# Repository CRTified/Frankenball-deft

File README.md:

# Frankenball-deft

This project is a replacement PCB for the Elecom Deft (non-pro) trackball.
Besides the basic functionality, it exposes two additional GPIO pins 
(also usable for debugging) and is powered by QMK (TODO) on an STM32F411.

The sensor used in the Elecom deft is an PWM3320.

Some additional soldering is required. 
The PCB is intended for SMT assembly by JLCPCB. 
The only extended part is the STM32F411, every other part is a basic component.

## Additional componens used

 - 0.5mm 6pin Clamshell FFC connector (PWM3320 Sensor)
   - https://aliexpress.com/item/1005003981823532.html
 - 0.5mm 12pin Clamshell FFC connector (Side button daughterboard)
   - https://aliexpress.com/item/1005003981823532.html
 - 4 pin JST ZH header (1.5mm pitch) (M1/M2/M3 daughterboard)
   - https://aliexpress.com/item/32763788431.html
 - 51146 Socket (USB connection)
   - https://aliexpress.com/item/4000818221650.html
 - Microswitch (Right mouse button)
   - https://aliexpress.com/item/4000682779339.html
   - https://aliexpress.com/item/4000555763322.html

## Rendered PCB

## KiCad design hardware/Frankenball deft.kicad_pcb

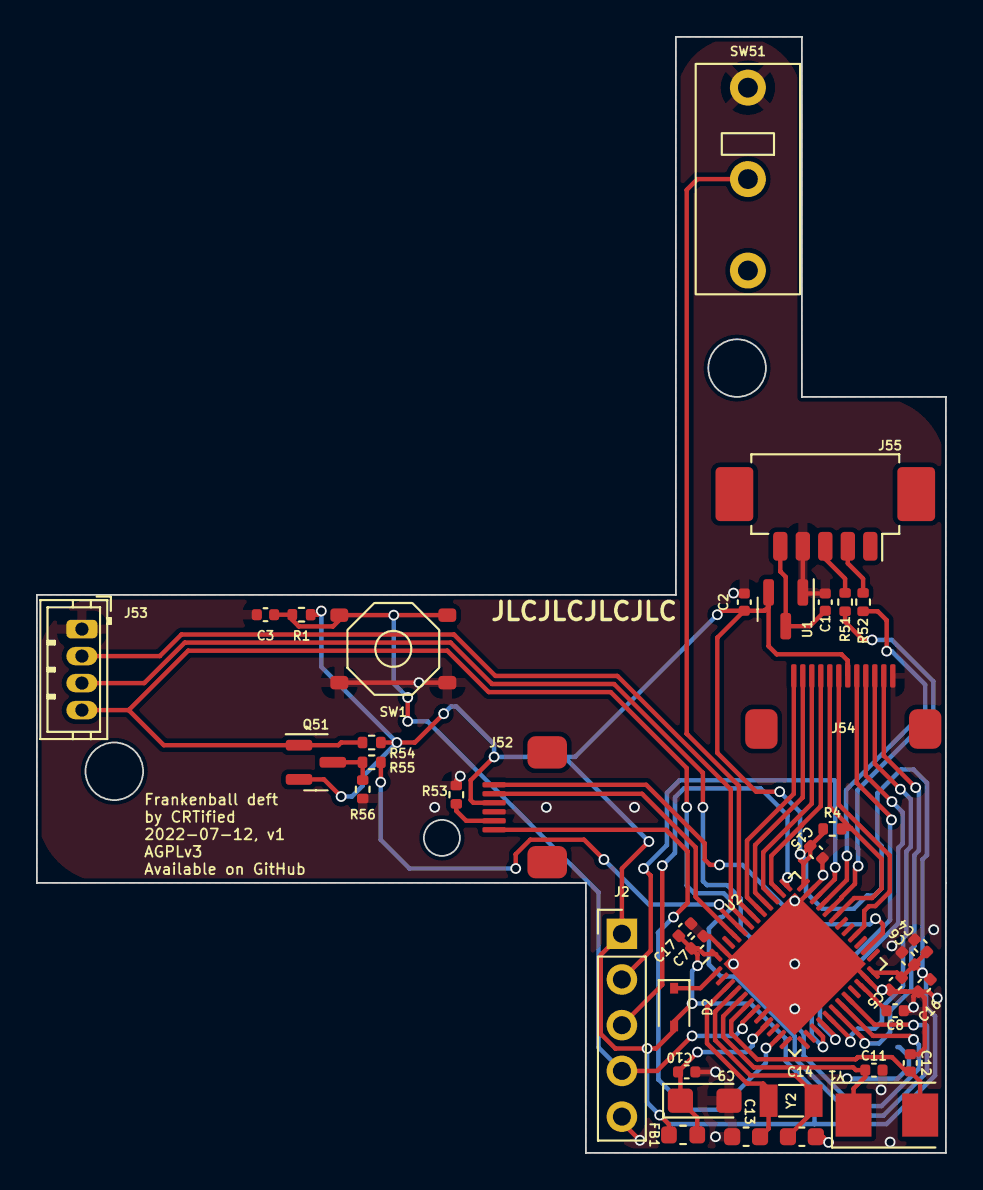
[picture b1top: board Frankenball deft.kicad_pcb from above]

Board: 2 copper layers, 50.5 x 62.0 mm, 39 parts (0 on the bottom side), 37 nets.

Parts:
C1, C2: 1µF; C_0402_1005Metric
C3, C4, C5, C6, C7, C10, C15, C16: 100nF; C_0402_1005Metric
C8: 4.7µF; C_0402_1005Metric
C9: 10µF; CP_EIA-3216-10_Kemet-I
C11, C12: 22pF; C_0402_1005Metric
C13, C14: 10pF; C_0603_1608Metric
C17: 4.7uF; C_0402_1005Metric
D2: D_Schottky; D_SOD-323
FB1: 600Ω@100MHz; L_0603_1608Metric
J2: Connector_Generic:Conn_01x05; PinHeader_1x05_P2.54mm_Vertical
J52: PWM3320; FFC Clamshell 0.5mm 6P
J53: Conn_01x04_Male; JST_ZH_B4B-ZR_1x04_P1.50mm_Vertical
J54: Conn_01x12; FFC Clamshell 0.5mm 12P
J55: Conn_01x05_Female; Molex_PicoBlade_53261-0571_1x05-1MP_P1.25mm_Horizontal
Q51: AO3401A; SOT-23
R1: 22kΩ; R_0402_1005Metric
R4: 100k; R_0402_1005Metric
R51, R52: 100Ω; R_0402_1005Metric
R53, R54, R55, R56: 10k; R_0402_1005Metric
SW1: SW_Push; TS-1187A-B-A-B
SW51: SW_Push; Mouse Microswitch SPDT
U1: XC6206PxxxMR; SOT-23
U2: STM32F411CCUx; QFN-48-1EP_7x7mm_P0.5mm_EP5.6x5.6mm
Y1: 8MHz; Crystal_SMD_5032-2Pin_5.0x3.2mm
Y2: 32.768kHz; Crystal_SMD_3215-2Pin_3.2x1.5mm

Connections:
+3.3V: C2.1, C4.1, C5.1, C6.1, C7.1, C15.1, C16.1, C17.1, D2.2 (A), FB1.1, J2.1, J52.4, J54.7, Q51.2 (S), R1.1, R4.2, R54.2, U1.2 (VO), U2.24 (VDD), U2.36 (VDD), U2.48 (VDD)
/BOOT0: R55.1, U2.44 (BOOT0)
/STM32F411/PA1: J52.1, U2.11 (PA1)
/STM32F411/PA5: J54.8, U2.15 (PA5)
/STM32F411/PA6: J54.9, U2.16 (PA6)
/STM32F411/PA7: J54.10, U2.17 (PA7)
/STM32F411/PA10: J54.5, R4.1, U2.31 (PA10)
/STM32F411/PA11: R51.1, U2.32 (PA11)
/STM32F411/PA12: R52.1, U2.33 (PA12)
/STM32F411/PA13: J2.2, U2.34 (PA13)
/STM32F411/PA14: J2.3, U2.37 (PA14)
/STM32F411/PA15: J54.4, U2.38 (PA15)
/STM32F411/PB0: J54.11, U2.18 (PB0)
/STM32F411/PB1: J53.3, U2.19 (PB1)
/STM32F411/PB2: J53.4, Q51.1 (G), R54.1, U2.20 (PB2)
/STM32F411/PB3: J54.3, U2.39 (PB3)
/STM32F411/PB4: J54.2, U2.40 (PB4)
/STM32F411/PB5: J54.1, U2.41 (PB5)
/STM32F411/PB6: SW51.3 (C), U2.42 (PB6)
/STM32F411/PB7: J53.2, U2.43 (PB7)
/STM32F411/PB8: J52.5, U2.45 (PB8)
/STM32F411/PBu13: J52.6, U2.26 (PB13)
/STM32F411/PBu15: J54.6, U2.28 (PB15)
/STM32F411/VBAT_{I}: D2.1 (K), U2.1 (VBAT)
/STM32F411/VREF+: C9.1, C10.1, FB1.2, U2.9 (VDDA)
/STM32F411/XTAL_8M_1: C11.1, U2.5 (PH0), Y1.1
/STM32F411/XTAL_8M_2: C12.1, U2.6 (PH1), Y1.2
/STM32F411/XTAL_32K_1: C13.1, U2.3 (PC14), Y2.1
/STM32F411/XTAL_32K_2: C14.1, U2.4 (PC15), Y2.2
/STM32F411/~RST_{I}: C3.1, J2.4, R1.2, SW1.2, U2.7 (NRST)
/USB_DM: J55.3, R51.2
/USB_DP: J55.2, R52.2
/~CS: J52.2, R53.2
GND: C1.2, C2.2, C3.2, C4.2, C5.2, C6.2, C7.2, C8.2, C9.2, C10.2, C11.2, C12.2, C13.2, C14.2, C15.2, C16.2, C17.2, J2.5, J52.3, J53.1, J54.12, J55.4, R53.1, R56.1, SW1.1, SW51.2 (B), U1.1 (GND), U2.8 (VSSA), U2.23 (VSS), U2.35 (VSS), U2.47 (VSS), U2.49 (VSS)
unnamed: C8.1, U2.22 (VCAP1)
unnamed: Q51.3 (D), R55.2, R56.2
VCC: C1.1, J55.5, U1.3 (VI)

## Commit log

2022-06-23 Initial Schematics commit
2022-07-11 Am I done?
2022-07-11 Replace boot config header with PFET
2022-07-18 Update symbol
2022-07-21 Add fabrication files

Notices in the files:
hardware/Frankenball deft.kicad_pcb:
AGPLv3
